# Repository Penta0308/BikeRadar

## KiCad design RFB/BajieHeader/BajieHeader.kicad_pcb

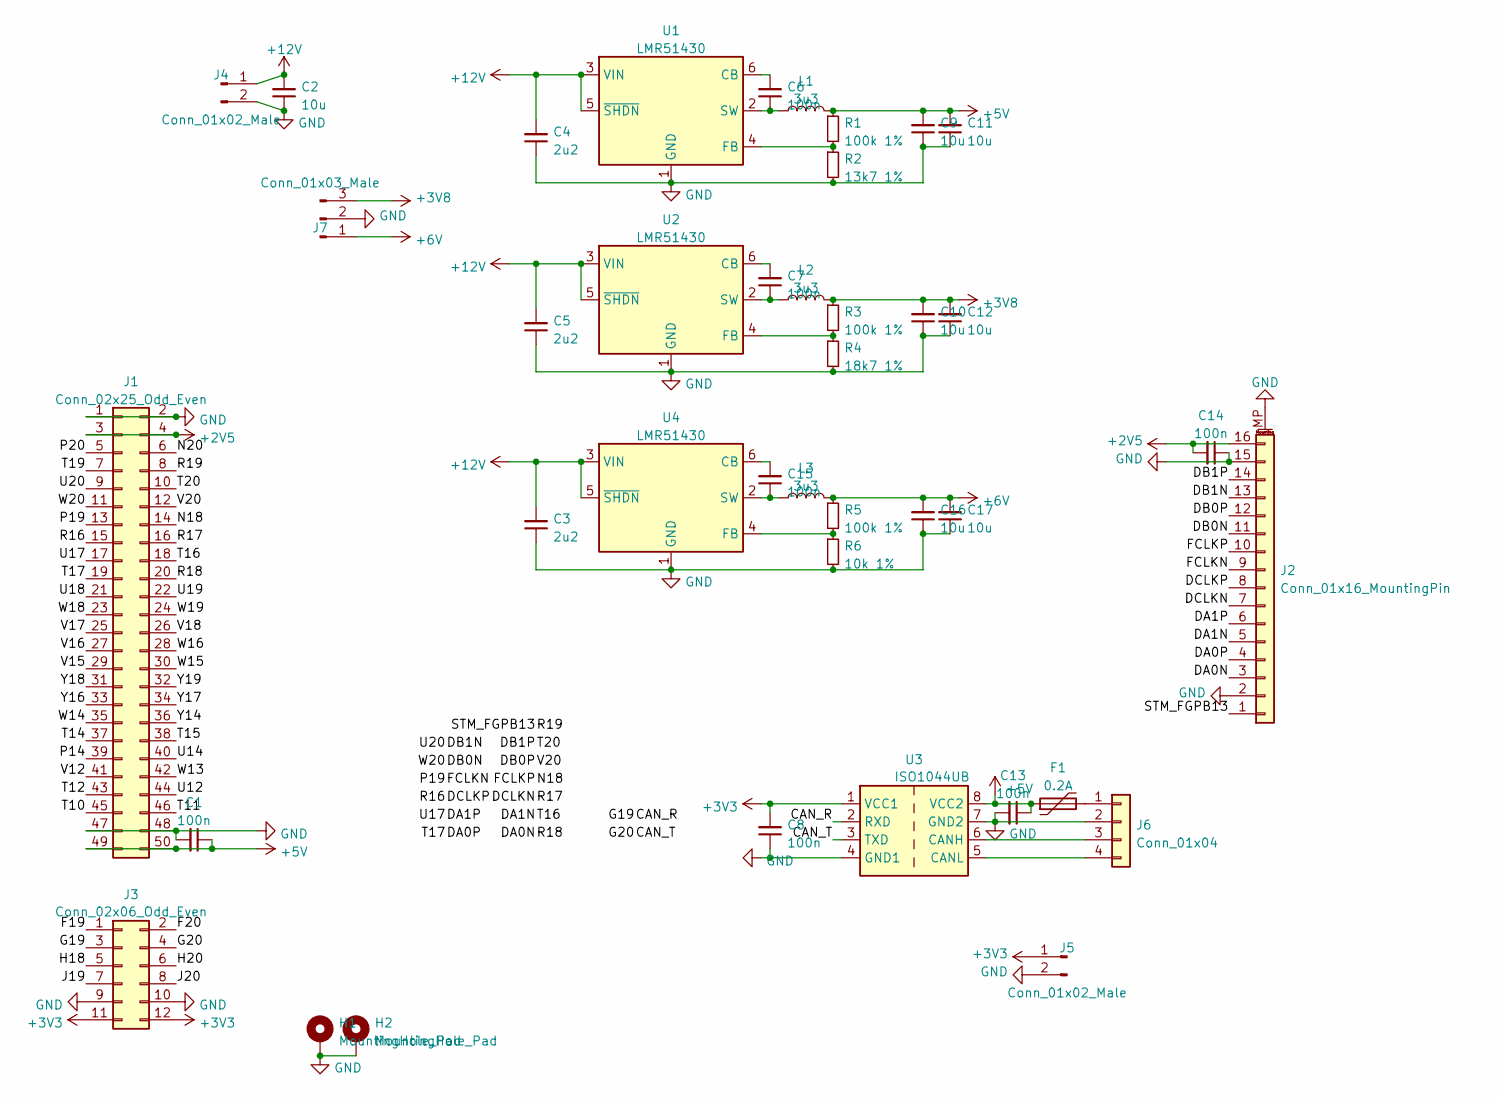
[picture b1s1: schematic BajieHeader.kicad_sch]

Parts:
C1, C6, C7, C8, C13, C14, C15: 100n; C_0402_1005Metric
C2, C9, C10, C11, C12, C16, C17: 10u; C_0603_1608Metric
C3, C4, C5: 2u2; C_0603_1608Metric
F1: 0.2A; Fuse_1206_3216Metric
H1, H2: MountingHole_Pad; MountingHole_2.2mm_M2_ISO7380_Pad_TopBottom
J1: Conn_02x25_Odd_Even; PinHeader_2x25_P2.54mm_Vertical
J2: Conn_01x16_MountingPin; TE_1-1734839-6_1x16-1MP_P0.5mm_Horizontal
J3: Conn_02x06_Odd_Even; PinHeader_2x06_P2.54mm_Vertical
J4, J5: Conn_01x02_Male; PinHeader_1x02_P2.54mm_Vertical
J6: Conn_01x04; PinHeader_1x04_P1.27mm_Vertical
J7: Conn_01x03_Male; PinHeader_1x03_P2.54mm_Vertical
L1, L2, L3: 3u3; SRP3212A
R1, R3, R5: 100k 1%; R_0402_1005Metric
R2: 13k7 1%; R_0402_1005Metric
R4: 18k7 1%; R_0402_1005Metric
R6: 10k 1%; R_0402_1005Metric
U1, U2, U4: LMR51430; SOT-23-6
U3: ISO1044UB; SOIC-8_3.9x4.9mm_P1.27mm

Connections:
+2V5: C14.2, J1.3, J1.4, J2.16
+3V3: C8.2, J3.11, J3.12, J5.1, U3.1 (VCC1)
+3V8: C10.2, C12.2, J7.3, L2.2, R3.1
+5V: C1.1, C9.2, C11.2, C13.1, F1.1, J1.49, J1.50, L1.2, R1.1, U3.8 (VCC2)
+6V: C16.2, C17.2, J7.1, L3.2, R5.1
+12V: C2.2, C3.2, C4.2, C5.2, J4.1, U1.3 (VIN), U1.5 (~SHDN), U2.3 (VIN), U2.5 (~SHDN), U4.3 (VIN), U4.5 (~SHDN)
/CAN_R: J3.3, U3.2 (RXD)
/CAN_T: J3.4, U3.3 (TXD)
/DA0N: J1.20, J2.3
/DA0P: J1.19, J2.4
/DA1N: J1.18, J2.5
/DA1P: J1.17, J2.6
/DB0N: J1.11, J2.11
/DB0P: J1.12, J2.12
/DB1N: J1.9, J2.13
/DB1P: J1.10, J2.14
/DCLKN: J1.16, J2.7
/DCLKP: J1.15, J2.8
/F19: J3.1
/F20: J3.2
/FCLKN: J1.13, J2.9
/FCLKP: J1.14, J2.10
/H18: J3.5
/H20: J3.6
/J19: J3.7
/J20: J3.8
/N20: J1.6
/P14: J1.39
/P20: J1.5
/R19: J1.8, J2.1
/T10: J1.45
/T11: J1.46
/T12: J1.43
/T14: J1.37
/T15: J1.38
/T19: J1.7
/U12: J1.44
/U14: J1.40
/U18: J1.21
/U19: J1.22
/V12: J1.41
/V15: J1.29
/V16: J1.27
/V17: J1.25
/V18: J1.26
/W13: J1.42
/W14: J1.35
/W15: J1.30
/W16: J1.28
/W18: J1.23
/W19: J1.24
/Y14: J1.36
/Y16: J1.33
/Y17: J1.34
/Y18: J1.31
/Y19: J1.32
GND: C1.2, C2.1, C3.1, C4.1, C5.1, C8.1, C9.1, C10.1, C11.1, C12.1, C13.2, C14.1, C16.1, C17.1, H1.1, H2.1, J1.1, J1.2, J1.47, J1.48, J2.2, J2.15, J2.MP (MountPin), J3.9, J3.10, J4.2, J5.2, J6.2, J7.2, R2.2, R4.2, R6.2, U1.1 (GND), U2.1 (GND), U3.4 (GND1), U3.7 (GND2), U4.1 (GND)
unnamed: C6.1, L1.1, U1.2 (SW)
unnamed: C6.2, U1.6 (CB)
unnamed: C7.1, L2.1, U2.2 (SW)
unnamed: C7.2, U2.6 (CB)
unnamed: C15.1, L3.1, U4.2 (SW)
unnamed: C15.2, U4.6 (CB)
unnamed: F1.2, J6.1
unnamed: J6.3, U3.6 (CANH)
unnamed: J6.4, U3.5 (CANL)
unnamed: R1.2, R2.1, U1.4 (FB)
unnamed: R3.2, R4.1, U2.4 (FB)
unnamed: R5.2, R6.1, U4.4 (FB)

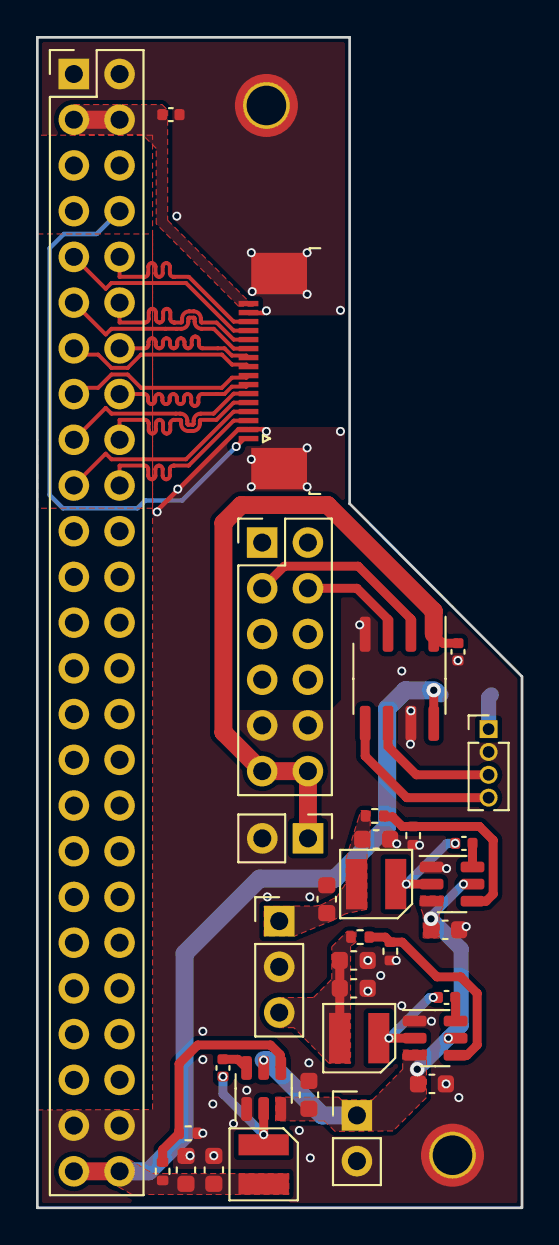
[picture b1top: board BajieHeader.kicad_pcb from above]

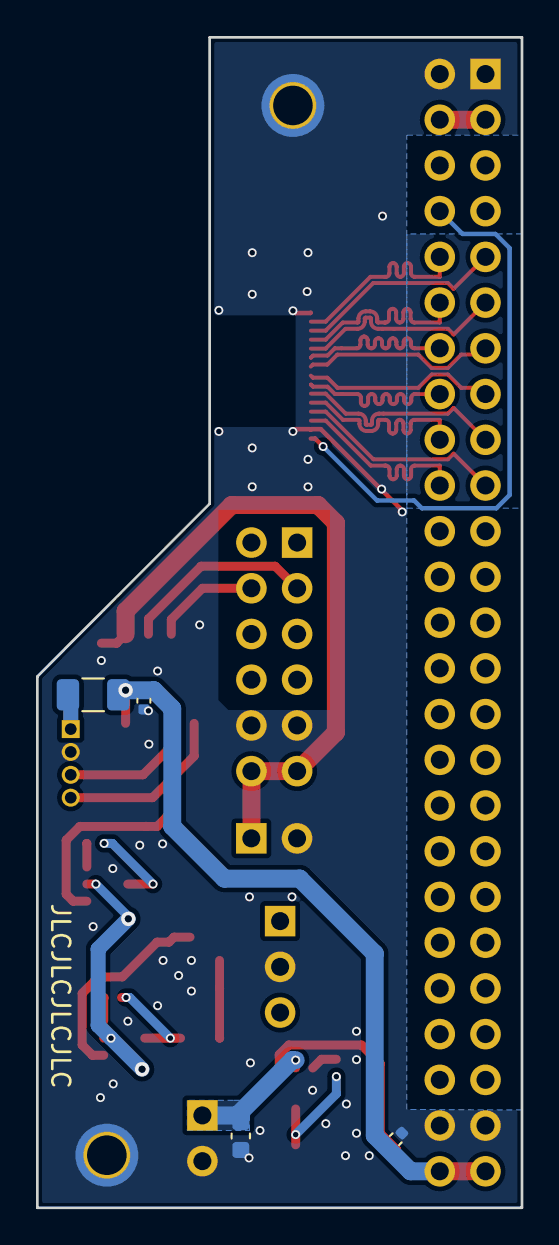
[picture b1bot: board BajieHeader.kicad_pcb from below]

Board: 2 copper layers, 26.9 x 65.0 mm, 40 parts (4 on the bottom side), 34 nets.

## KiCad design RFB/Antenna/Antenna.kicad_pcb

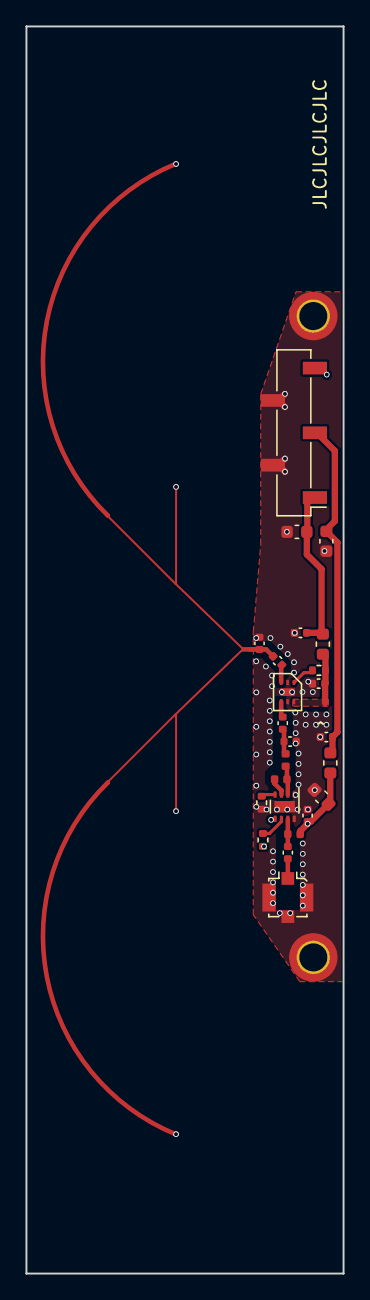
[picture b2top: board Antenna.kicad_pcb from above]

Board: 4 copper layers, 24.9 x 97.9 mm, 27 parts (1 on the bottom side), 17 nets.

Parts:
AE1: Antenna; Antenna_PatchArray4_JLC7628_1.6_5800M
C1, C3, C6: 100n; C_0402_1005Metric
C2, C13: 10u; C_0603_1608Metric
C4: 0.5p R; C_0402_1005Metric
C5: 22p R; C_0402_1005Metric
C8: 4p3 R; C_0402_1005Metric
C9: 0.4p R; C_0402_1005Metric
C10: 5p6; C_0402_1005Metric
C11: 2p2 R; C_0402_1005Metric
C12: 4u7; C_0603_1608Metric
FB1, FB2: BLM18PG181SN1D; L_0603_1608Metric
H1, H2: MountingHole_Pad; MountingHole_2.2mm_M2_ISO14580_Pad_TopOnly
IC2: SKY67189-396LF; WSON-8-1EP_2x2mm_P0.5mm_EP0.9x1.6mm
J1: Conn_Coaxial; U.FL_Molex_MCRF_73412-0110_Vertical
J2: Conn_01x05_Male; PinSocket_1x05_P2.54mm_Vertical_SMD_Pin1Left
L1: 400p R; L_0402_1005Metric
L2: 6n8; L_0402_1005Metric
L3: 2n4 R; L_0402_1005Metric
R2: 3k; R_0402_1005Metric
R3: 5k1; R_0402_1005Metric
R4: 20; R_0402_1005Metric
U3: GRF2101; DFN-6-1.5x1.5_1EP

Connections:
/3V3A: C6.1, FB1.1, R2.2, U3.6 (VCC)
/5VA: C10.2, C12.2, FB2.1, L3.2, R4.2
/receiver/RF_OUT: C11.2, J1.1 (In)
/receiver/RX: AE1.1 (A), C4.2, C5.1
/~EN1: IC2.5 (~EN), J2.5
GND: C1.2, C2.2, C3.2, C4.1, C6.2, C9.1, C10.1, C12.1, C13.2, H1.1, H2.1, IC2.1 (N/C), IC2.8 (N/C), IC2.9 (EP), J1.2 (Ext), J2.2, J2.4, R3.2, U3.2 (GND), U3.5 (GND), U3.7 (EP)
unnamed: C5.2, U3.3 (RFIN)
unnamed: C8.1, U3.4 (RFOUT)
unnamed: C8.2, C9.2, L1.1
unnamed: C11.1, IC2.7 (RFOUT), L3.1
unnamed: IC2.2 (RFIN), L1.2, L2.1
unnamed: IC2.3 (VBIAS), L2.2
unnamed: IC2.4 (RSET), R3.1
unnamed: IC2.6 (VDD), R4.1
unnamed: C1.1, C2.1, FB1.2, J2.1
unnamed: C3.1, C13.1, FB2.2, J2.3
unnamed: R2.1, U3.1 (VENABLE)

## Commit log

2023-06-01 no rtos
